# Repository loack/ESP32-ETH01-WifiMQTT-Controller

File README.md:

# ESP32-ETH01-WifiMQTT-Controller

Contrôleur générique d'I/O pour WT32-ETH01 avec Ethernet prioritaire et fallback WiFi.

## Description

Ce projet est basé sur le ESP32-WifiMQTTRelay avec les adaptations suivantes pour la board WT32-ETH01:
- **Ethernet par défaut**: Connexion Ethernet prioritaire pour une latence minimale
- **Fallback WiFi**: Bascule automatique sur WiFi si Ethernet échoue
- **MQTT**: Contrôle et monitoring via MQTT avec synchronisation temporelle microseconde
- **Interface Web**: Configuration complète via interface web (SPIFFS)
- **I/O configurables**: Jusqu'à 20 I/O configurables (entrées/sorties)
- **OTA**: Mise à jour Over-The-Air via ElegantOTA

## Caractéristiques

### Réseau
- **Ethernet WT32-ETH01 (LAN8720)** - Connexion prioritaire
- **WiFi** - Fallback automatique avec WiFiManager
- **IP statique ou DHCP** - Configurable
- **MQTT** - Contrôle temps réel avec précision microseconde
- **Synchronisation temporelle** - Via MQTT (précision μs)

### I/O
- **Entrées**: INPUT, INPUT_PULLUP, INPUT_PULLDOWN
- **Sorties**: Avec état par défaut configurable
- **Détection de changement**: Réactivité 1ms via tâche FreeRTOS
- **Commandes programmées**: Exécution avec précision microseconde

### Interface
- **Web UI**: Configuration complète depuis le navigateur
- **API REST**: Contrôle et statut en JSON
- **OTA**: Mises à jour firmware via web

### Pont Série (Serial Bridge)

- **Serial Bridge (RS232/RS485)**: Le contrôleur peut acheminer des messages série vers/depuis un port UART (utilise `Serial2`).
- **Usage principal**: Permet d'envoyer des messages série (ex. format RS232 pour KUKA VKRC2) et de consulter un journal des échanges depuis l'interface Web ou via l'API REST.
- **Pins configurables**: Broches RX/TX configurables depuis l'interface (par défaut `RX=4`, `TX=5`).
- **Paramètres**: Activation, `baudrate`, `RX`, `TX` sont persistés dans Preferences.

## Configuration Matérielle

### WT32-ETH01
- **Ethernet**: PHY LAN8720
  - MDC: GPIO 23
  - MDIO: GPIO 18
  - Power: GPIO 16
  - CLK: GPIO 0
- **LED Status**: GPIO 2
- **Bouton BOOT**: GPIO 0 (triple-press pour reset WiFi)

### GPIO Disponibles
Les GPIO suivants sont disponibles pour configuration:
- GPIO 4, 5, 12, 13, 14, 15, 17, 32, 33

**⚠️ GPIO Réservés:**
- 0, 2, 16, 18, 23 (Ethernet + LED)

## Installation

### PlatformIO

## API MQTT

La communication avec le module via MQTT est documentée dans le fichier [MQTT_API.md](MQTT_API.md).
```bash
# Cloner le projet
cd ESP32-ETH01-WifiMQTT-Controller

# Compiler et uploader
pio run -t upload

# Uploader le système de fichiers SPIFFS
pio run -t uploadfs

# Monitor série
pio device monitor -b 115200
```

## Configuration

### Première utilisation
1. Connecter le câble Ethernet
2. Le système démarre automatiquement en mode Ethernet
3. Accéder à l'interface web via l'IP DHCP ou IP statique configurée
4. Configurer les I/O, MQTT et autres paramètres

### Fallback WiFi
Si Ethernet échoue:
1. Le système bascule automatiquement sur WiFi
2. Un portail captif s'ouvre: **ESP32-Controller-Setup**
3. Connecter au WiFi et configurer les credentials
4. L'appareil redémarre et se connecte au WiFi

### Reset WiFi
Triple-appui sur le bouton BOOT dans les 5 secondes au démarrage pour effacer les credentials WiFi.

## API REST

### Statut
```http
GET /api/status
```
Retourne le statut complet du système (réseau, MQTT, I/O, heure)

### Contrôle I/O
```http
POST /api/io/set
Content-Type: application/json

{
  "name": "relay1",
  "state": true
}
```

### Configuration I/O
```http
GET /api/ios
POST /api/ios
```

### Configuration Système
```http
GET /api/config
POST /api/config
```

La configuration système expose désormais les paramètres du pont série:

- `useSerialBridge` (bool): activer/désactiver le pont série
- `serialRxPin` (int): broche RX utilisée par `Serial2`
- `serialTxPin` (int): broche TX utilisée par `Serial2`
- `serialBaudRate` (int): vitesse en bauds

Exemple payload pour `POST /api/config` (JSON):

```json
{
  "useSerialBridge": true,
  "serialRxPin": 4,
  "serialTxPin": 5,
  "serialBaudRate": 9600
}
```

### Pont Série — Envoi de message
```http
POST /api/serial/send
Content-Type: application/json

{ "message": "...\n" }
```
Envoie la chaîne fournie au port série (ajoute un saut de ligne si nécessaire). Retourne JSON `{ "success": true }` en cas de succès.

### Pont Série — Récupération des logs
```http
GET /api/serial/logs
```
Retourne un tableau JSON de logs série (timestamp, direction `TX|RX`, message).

## MQTT

### Topics

#### Contrôle
```
{deviceName}/control/{ioName}/set
Payload: {"state": 1, "exec_at": 1234567890, "exec_at_us": 123456}
```

#### Statut
```
{deviceName}/status/{ioName}
Payload: {"state": 1, "timestamp": 1234567890, "us": 123456}
```

#### Synchronisation temporelle
```
esp32/time/sync
Payload: {"seconds": 1234567890, "us": 123456, "compensations": {...}}
```

#### Mesure latence
```
{deviceName}/ping
{deviceName}/pong
```

## Dépendances

- ESP32 Arduino Core
- ESPAsyncWebServer
- AsyncTCP
- ArduinoJson 7.x
- PubSubClient (MQTT)
- WiFiManager
- ElegantOTA
- NTPClient

## Notes sur la configuration du Pont Série

- Les préférences sont sauvegardées sous les clés: `useSerial` (bool), `serRx` (int), `serTx` (int), `serBaud` (long).
- Par défaut, si `useSerial` = `false`, le port série externe n'est pas initialisé.
- Le gestionnaire série utilise `Serial2`; vérifiez la compatibilité des broches sur votre WT32-ETH01 avant d'assigner des GPIO réservés (voir section GPIO Disponibles / Réservés).

## Différences avec ESP32-WifiMQTTRelay

1. **Ethernet prioritaire**: WT32-ETH01 démarre en mode Ethernet par défaut
2. **LED Status**: GPIO 2 au lieu de GPIO 23
3. **Nom par défaut**: `esp32-eth01` au lieu de `esp32`
4. **Config automatique**: Force le mode Ethernet au premier démarrage

## Licence

Ce projet est dérivé de ESP32-WifiMQTTRelay et adapté pour WT32-ETH01.

## Notes

- La LED sur GPIO 2 indique le statut (clignotements pendant l'initialisation)
- Ethernet est prioritaire sur WiFi pour une latence minimale
- Le fallback WiFi permet une haute disponibilité
- La synchronisation temporelle MQTT permet une précision microseconde
- Les commandes programmées sont exécutées avec précision microseconde
# ESP32-ETH01-WifiMQTT-Controller

Contrôleur générique d'I/O pour WT32-ETH01 avec Ethernet prioritaire et fallback WiFi.

## Description

Ce projet est basé sur le ESP32-WifiMQTTRelay avec les adaptations suivantes pour la board WT32-ETH01:
- **Ethernet par défaut**: Connexion Ethernet prioritaire pour une latence minimale
- **Fallback WiFi**: Bascule automatique sur WiFi si Ethernet échoue
- **MQTT**: Contrôle et monitoring via MQTT avec synchronisation temporelle microseconde
- **Interface Web**: Configuration complète via interface web (SPIFFS)
- **I/O configurables**: Jusqu'à 20 I/O configurables (entrées/sorties)
- **OTA**: Mise à jour Over-The-Air via ElegantOTA

## Caractéristiques

### Réseau
- **Ethernet WT32-ETH01 (LAN8720)** - Connexion prioritaire
- **WiFi** - Fallback automatique avec WiFiManager
- **IP statique ou DHCP** - Configurable
- **MQTT** - Contrôle temps réel avec précision microseconde
- **Synchronisation temporelle** - Via MQTT (précision μs)

### I/O
- **Entrées**: INPUT, INPUT_PULLUP, INPUT_PULLDOWN
- **Sorties**: Avec état par défaut configurable
- **Détection de changement**: Réactivité 1ms via tâche FreeRTOS
- **Commandes programmées**: Exécution avec précision microseconde

### Interface
- **Web UI**: Configuration complète depuis le navigateur
- **API REST**: Contrôle et statut en JSON
- **OTA**: Mises à jour firmware via web

## Configuration Matérielle

### WT32-ETH01
- **Ethernet**: PHY LAN8720
  - MDC: GPIO 23
  - MDIO: GPIO 18
  - Power: GPIO 16
  - CLK: GPIO 0
- **LED Status**: GPIO 2
- **Bouton BOOT**: GPIO 0 (triple-press pour reset WiFi)

### GPIO Disponibles
Les GPIO suivants sont disponibles pour configuration:
- GPIO 4, 5, 12, 13, 14, 15, 17, 32, 33

**⚠️ GPIO Réservés:**
- 0, 2, 16, 18, 23 (Ethernet + LED)

## Installation

### PlatformIO

## API MQTT

La communication avec le module via MQTT est documentée dans le fichier [MQTT_API.md](MQTT_API.md).
```bash
# Cloner le projet
cd ESP32-ETH01-WifiMQTT-Controller

# Compiler et uploader
pio run -t upload

# Uploader le système de fichiers SPIFFS
pio run -t uploadfs

# Monitor série
pio device monitor -b 115200
```

## Configuration

### Première utilisation
1. Connecter le câble Ethernet
2. Le système démarre automatiquement en mode Ethernet
3. Accéder à l'interface web via l'IP DHCP ou IP statique configurée
4. Configurer les I/O, MQTT et autres paramètres

### Fallback WiFi
Si Ethernet échoue:
1. Le système bascule automatiquement sur WiFi
2. Un portail captif s'ouvre: **ESP32-Controller-Setup**
3. Connecter au WiFi et configurer les credentials
4. L'appareil redémarre et se connecte au WiFi

### Reset WiFi
Triple-appui sur le bouton BOOT dans les 5 secondes au démarrage pour effacer les credentials WiFi.

## API REST

### Statut
```http
GET /api/status
```
Retourne le statut complet du système (réseau, MQTT, I/O, heure)

### Contrôle I/O
```http
POST /api/io/set
Content-Type: application/json

{
  "name": "relay1",
  "state": true
}
```

### Configuration I/O
```http
GET /api/ios
POST /api/ios
```

### Configuration Système
```http
GET /api/config
POST /api/config
```

## MQTT

### Topics

#### Contrôle
```
{deviceName}/control/{ioName}/set
Payload: {"state": 1, "exec_at": 1234567890, "exec_at_us": 123456}
```

#### Statut
```
{deviceName}/status/{ioName}
Payload: {"state": 1, "timestamp": 1234567890, "us": 123456}
```

#### Synchronisation temporelle
```
esp32/time/sync
Payload: {"seconds": 1234567890, "us": 123456, "compensations": {...}}
```

#### Mesure latence
```
{deviceName}/ping
{deviceName}/pong
```

## Dépendances

- ESP32 Arduino Core
- ESPAsyncWebServer
- AsyncTCP
- ArduinoJson 7.x
- PubSubClient (MQTT)
- WiFiManager
- ElegantOTA
- NTPClient

## Différences avec ESP32-WifiMQTTRelay

1. **Ethernet prioritaire**: WT32-ETH01 démarre en mode Ethernet par défaut
2. **LED Status**: GPIO 2 au lieu de GPIO 23
3. **Nom par défaut**: `esp32-eth01` au lieu de `esp32`
4. **Config automatique**: Force le mode Ethernet au premier démarrage

## Licence

Ce projet est dérivé de ESP32-WifiMQTTRelay et adapté pour WT32-ETH01.

## Notes

- La LED sur GPIO 2 indique le statut (clignotements pendant l'initialisation)
- Ethernet est prioritaire sur WiFi pour une latence minimale
- Le fallback WiFi permet une haute disponibilité
- La synchronisation temporelle MQTT permet une précision microseconde
- Les commandes programmées sont exécutées avec précision microseconde

# si 192.168.1.220 est directement joignable sur enp1s0
sudo ip route add 192.168.1.220/32 dev enp1s0
sudo ip route add 192.168.1.180/32 dev enp1s0

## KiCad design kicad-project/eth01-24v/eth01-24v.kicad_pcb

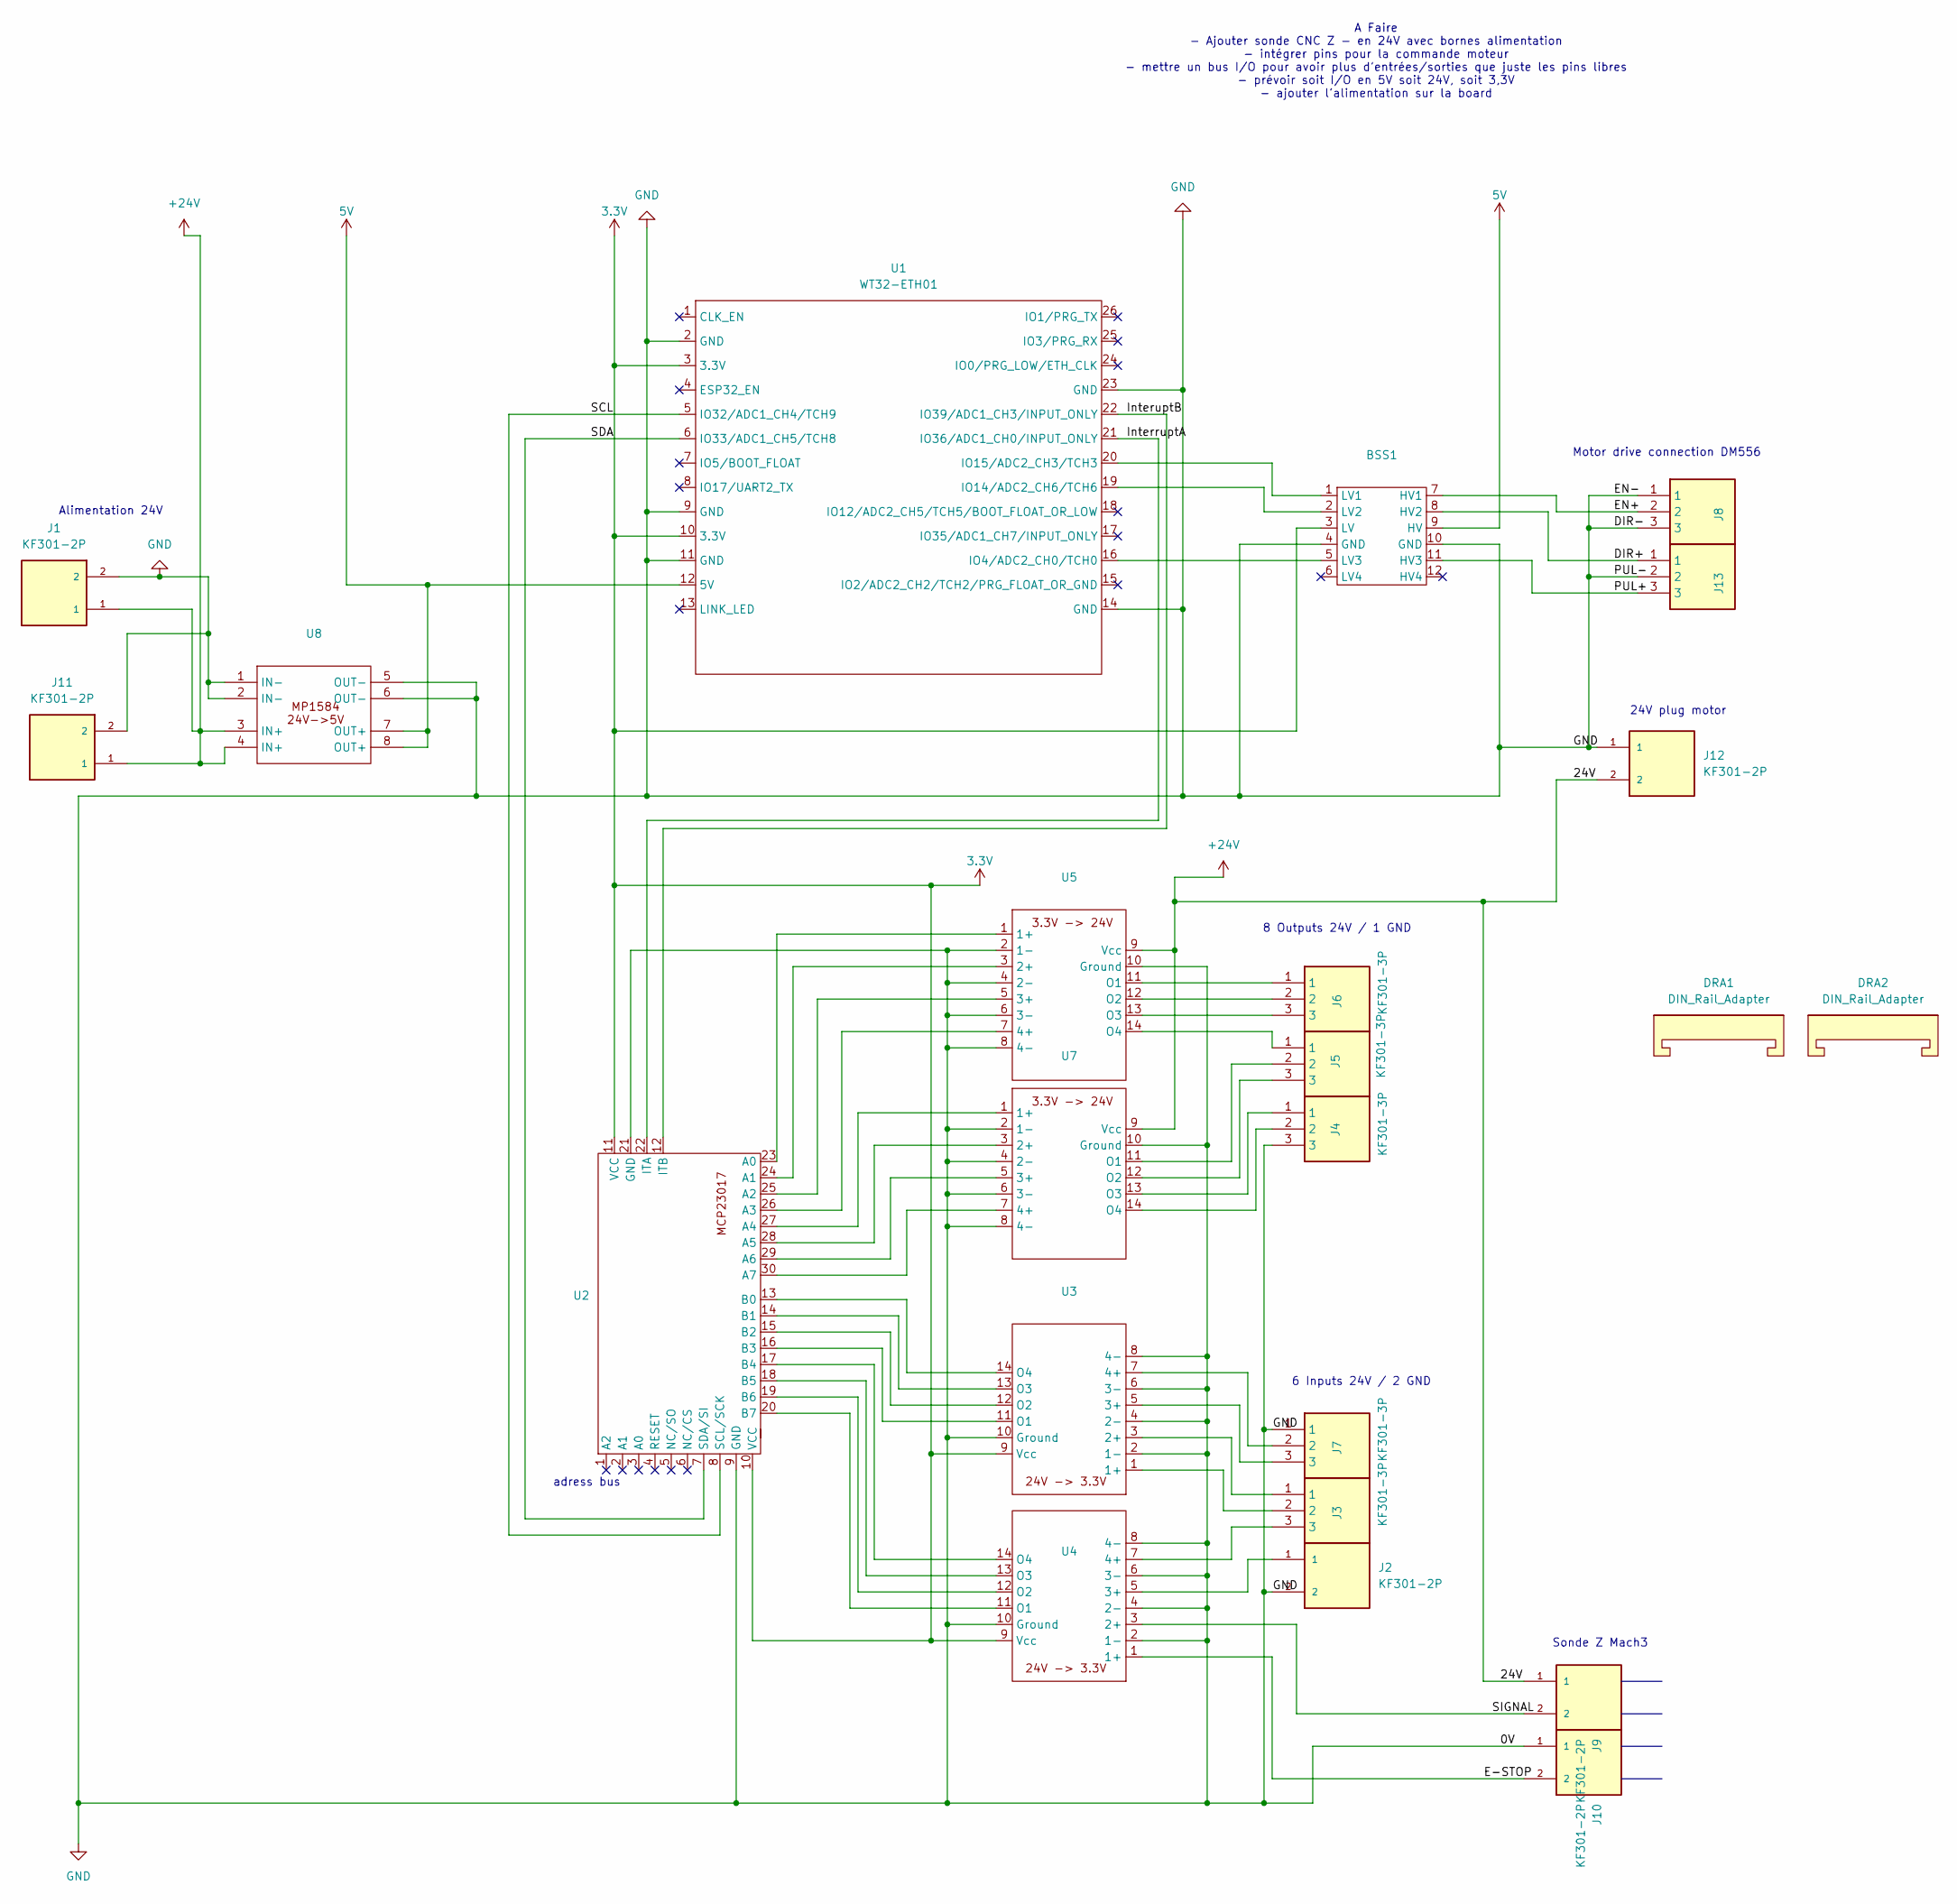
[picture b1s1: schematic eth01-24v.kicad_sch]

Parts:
BSS1: BSS138
DRA1, DRA2: DIN_Rail_Adapter; DINRailAdapter_3xM3_PhoenixContact_1201578
J1, J2, J9, J10, J11, J12: KF301-2P; KF3012P; PARTREV NA
J3, J4, J5, J6, J7, J8, J13: KF301-3P; KF3013P; Manufacturer_Part_Number KF301-3P
U1: WT32-ETH01
U2: MCP23017
U3, U4: OP71A04 - 24V3.3V
U5, U7: OP71A04 - 3.3V24V
U8: MP1584_AIO

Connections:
3.3V: BSS1.3 (LV), U1.3 (3.3V), U1.10 (3.3V), U2.10 (VCC), U2.11 (VCC), U3.9 (Vcc), U4.9 (Vcc)
5V: BSS1.9 (HV), U1.12 (5V), U8.7 (OUT+), U8.8 (OUT+)
+24V: J1.1, J9.1, J11.1, J12.2, U5.9 (Vcc), U7.9 (Vcc), U8.3 (IN+), U8.4 (IN+)
/DIR+: BSS1.8 (HV2), J13.1
/E-STOP: J10.2, U4.1 (1+)
/EN+: BSS1.7 (HV1), J8.2
/InterruptA: U1.21 (IO36/ADC1_CH0/INPUT_ONLY), U2.22 (ITA)
/InteruptB: U1.22 (IO39/ADC1_CH3/INPUT_ONLY), U2.12 (ITB)
/PUL+: BSS1.11 (HV3), J13.3
/SCL: U1.5 (IO32/ADC1_CH4/TCH9), U2.8 (SCL/SCK)
/SDA: U1.6 (IO33/ADC1_CH5/TCH8), U2.7 (SDA/SI)
/SIGNAL: J9.2, U4.3 (2+)
GND: BSS1.4 (GND), BSS1.10 (GND), J1.2, J2.2, J4.3, J7.1, J8.1, J8.3, J10.1, J11.2, J12.1, J13.2, U1.2 (GND), U1.9 (GND), U1.11 (GND), U1.14 (GND), U1.23 (GND), U2.9 (GND), U2.21 (GND), U3.2 (1-), U3.4 (2-), U3.6 (3-), U3.8 (4-), U3.10 (Ground), U4.2 (1-), U4.4 (2-), U4.6 (3-), U4.8 (4-), U4.10 (Ground), U5.2 (1-), U5.4 (2-), U5.6 (3-), U5.8 (4-), U5.10 (Ground), U7.2 (1-), U7.4 (2-), U7.6 (3-), U7.8 (4-), U7.10 (Ground), U8.1 (IN-), U8.2 (IN-), U8.5 (OUT-), U8.6 (OUT-)
unnamed: BSS1.1 (LV1), U1.20 (IO15/ADC2_CH3/TCH3)
unnamed: BSS1.2 (LV2), U1.19 (IO14/ADC2_CH6/TCH6)
unnamed: BSS1.5 (LV3), U1.16 (IO4/ADC2_CH0/TCH0)
unnamed: U2.26 (A3), U5.7 (4+)
unnamed: U2.27 (A4), U7.1 (1+)
unnamed: U2.28 (A5), U7.3 (2+)
unnamed: U2.29 (A6), U7.5 (3+)
unnamed: U2.30 (A7), U7.7 (4+)
unnamed: U2.13 (B0), U3.14 (O4)
unnamed: U2.14 (B1), U3.13 (O3)
unnamed: U2.15 (B2), U3.12 (O2)
unnamed: U2.16 (B3), U3.11 (O1)
unnamed: U2.17 (B4), U4.14 (O4)
unnamed: U2.18 (B5), U4.13 (O3)
unnamed: U2.19 (B6), U4.12 (O2)
unnamed: U2.20 (B7), U4.11 (O1)
unnamed: J3.2, U3.1 (1+)
unnamed: J3.1, U3.3 (2+)
unnamed: J7.3, U3.5 (3+)
unnamed: J7.2, U3.7 (4+)
unnamed: J2.1, U4.5 (3+)
unnamed: J3.3, U4.7 (4+)
unnamed: U2.23 (A0), U5.1 (1+)
unnamed: U2.24 (A1), U5.3 (2+)
unnamed: U2.25 (A2), U5.5 (3+)
unnamed: J6.1, U5.11 (O1)
unnamed: J6.2, U5.12 (O2)
unnamed: J6.3, U5.13 (O3)
unnamed: J5.1, U5.14 (O4)
unnamed: J5.2, U7.11 (O1)
unnamed: J5.3, U7.12 (O2)
unnamed: J4.1, U7.13 (O3)
unnamed: J4.2, U7.14 (O4)

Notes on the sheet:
Motor drive connection DM556
6 Inputs 24V / 2 GND
adress bus
8 Outputs 24V / 1 GND
Alimentation 24V
Sonde Z Mach3
24V plug motor
A Faire - Ajouter sonde CNC Z - en 24V avec bornes alimentation - intégrer pins pour la commande moteur - mettre un bus I/O pour avoir plus d'entrées/sorties que juste les pins libres - prévoir soit I/O en 5V soit 24V, soit 3,3V - ajouter l'alimentation sur la board

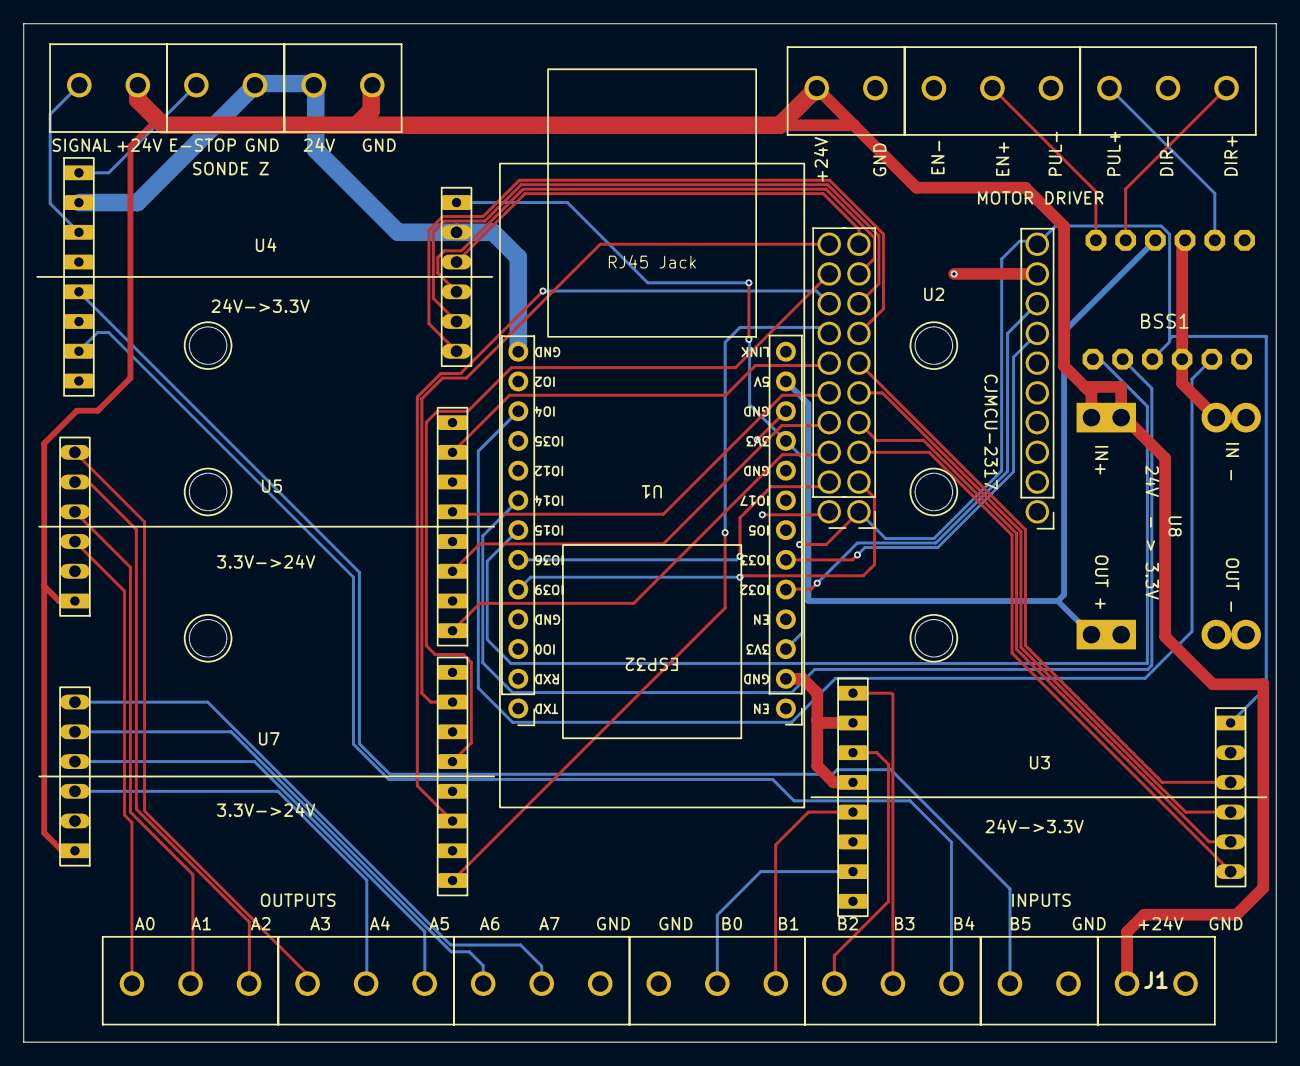
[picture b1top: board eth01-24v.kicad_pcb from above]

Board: 2 copper layers, 107.0 x 87.0 mm, 23 parts (0 on the bottom side), 46 nets.

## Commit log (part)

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2025-07-12 initial commit ESP32_ETH0
2025-07-12 working ethernet server but need to inverse state of relay
2025-07-12 added a simple python script to start and stop. change the inverse logic of the relay
2025-07-23 changed ip for second esp32
2025-11-15 adaptation du controlleur generic MQTT sur WT32-ETH01
2025-11-16 kicad project ajouté au repo
2025-11-17 Correction du fallback Wifi
2025-11-17 déplacement de l'appel de checkTriplePress() pour qu'il ne soit exécuté qu'au moment du fallback vers WiFi
2025-11-17 Config de la pin 39 pour le reset des wifi credentials plus fiable que IO0
2025-11-17 Modification pour que le serveur web fonctionne.
2025-11-18 Ajout de documentation
2025-11-21 feat(serial): add Serial Bridge (Serial2) support, web API and UI
    Ajout d'un pont série (Serial Bridge) utilisable pour communiquer avec des périphériques RS232/RS485 (ex: KUKA VKRC2).\n\nVoir le README pour la documentation des endpoints et des paramètres.
2025-11-21 Ajout de la gestion complète du pont série RS232 (Serial2) : configuration via web UI et API REST, envoi/réception de messages via MQTT, journalisation, avertissement sur l’utilisation de pins réserv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
2025-11-21 Add enhanced MQTT->Serial logging and Python serial-over-MQTT support
2025-11-21 serial: add debugging for Serial2 reads and MQTT publish attempts
2025-11-21 serial : version serial en test
2025-11-24 affichage de log WebSocket
2025-11-24 Modification du HTML pour utiliser WebSocket
2025-11-24 Interface de log complète avec les messages système et serial.
2025-11-24 légère modif de l'interface serial
2025-11-24 Amélioration de l'interface de test pour plus de clarté.
2026-01-02 ajout doc pins
2026-01-11 Harmonisation format payload MQTT IO (0/1 + timestamp us) et publication etat apres sync
2026-04-18 commit wsl
2026-05-29 ajout du projet de board modulable
2026-05-29 maj spec pour optocoupleurs
2026-05-31 ajout photos et première version pcb
2026-05-31 routage ok
2026-05-31 plan masse
2026-06-02 routage ok - silk screen corrigé- impression
